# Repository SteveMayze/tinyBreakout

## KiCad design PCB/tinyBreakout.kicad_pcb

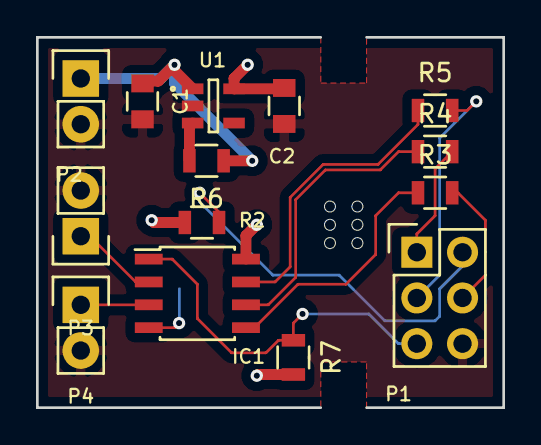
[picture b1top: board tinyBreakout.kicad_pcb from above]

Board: 2 copper layers, 25.9 x 20.6 mm, 15 parts (1 on the bottom side), 15 nets.

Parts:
C1, C2: 1μF; C_0805
C3: 100nF; C_0805
IC1: ATTINY13A-S; SOIC-8_3.9x4.9mm_Pitch1.27mm
P1: CONN_01X06; Pin_Header_Straight_2x03
P2, P3, P4: CONN_01X02; Pin_Header_Straight_1x02
R2, R3, R4, R5: 1kΩ; R_0805
R6: 0Ω; R_0805
R7: 10KΩ; R_0805
U1: LD2979; SOT-23-5L

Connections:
/Vin: C1.1, P2.1, R6.1, U1.1
GND: C1.2, C2.2, P1.6, P2.2, P3.2, P4.2, U1.2
MISO: IC1.6, R4.1
MOSI: IC1.5, R3.1
unnamed: C3.2, IC1.4
unnamed: P1.1, R4.2
unnamed: P1.2, R2.2
unnamed: P1.3, R5.2
unnamed: P1.4, R3.2
unnamed: R6.2, U1.3
PB3: IC1.2, P3.1
PB4: IC1.3, P4.1
RESET: IC1.1, P1.5, R7.1
SCK: IC1.7, R5.1
Vcc: C2.1, C3.1, IC1.8, R2.1, R7.2, U1.5

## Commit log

2015-10-28 Added a gitignore
2015-10-28 Added schematic and intial layout
2015-11-09 Upate to the schematic and layout
2016-01-08 Played around with the layout
